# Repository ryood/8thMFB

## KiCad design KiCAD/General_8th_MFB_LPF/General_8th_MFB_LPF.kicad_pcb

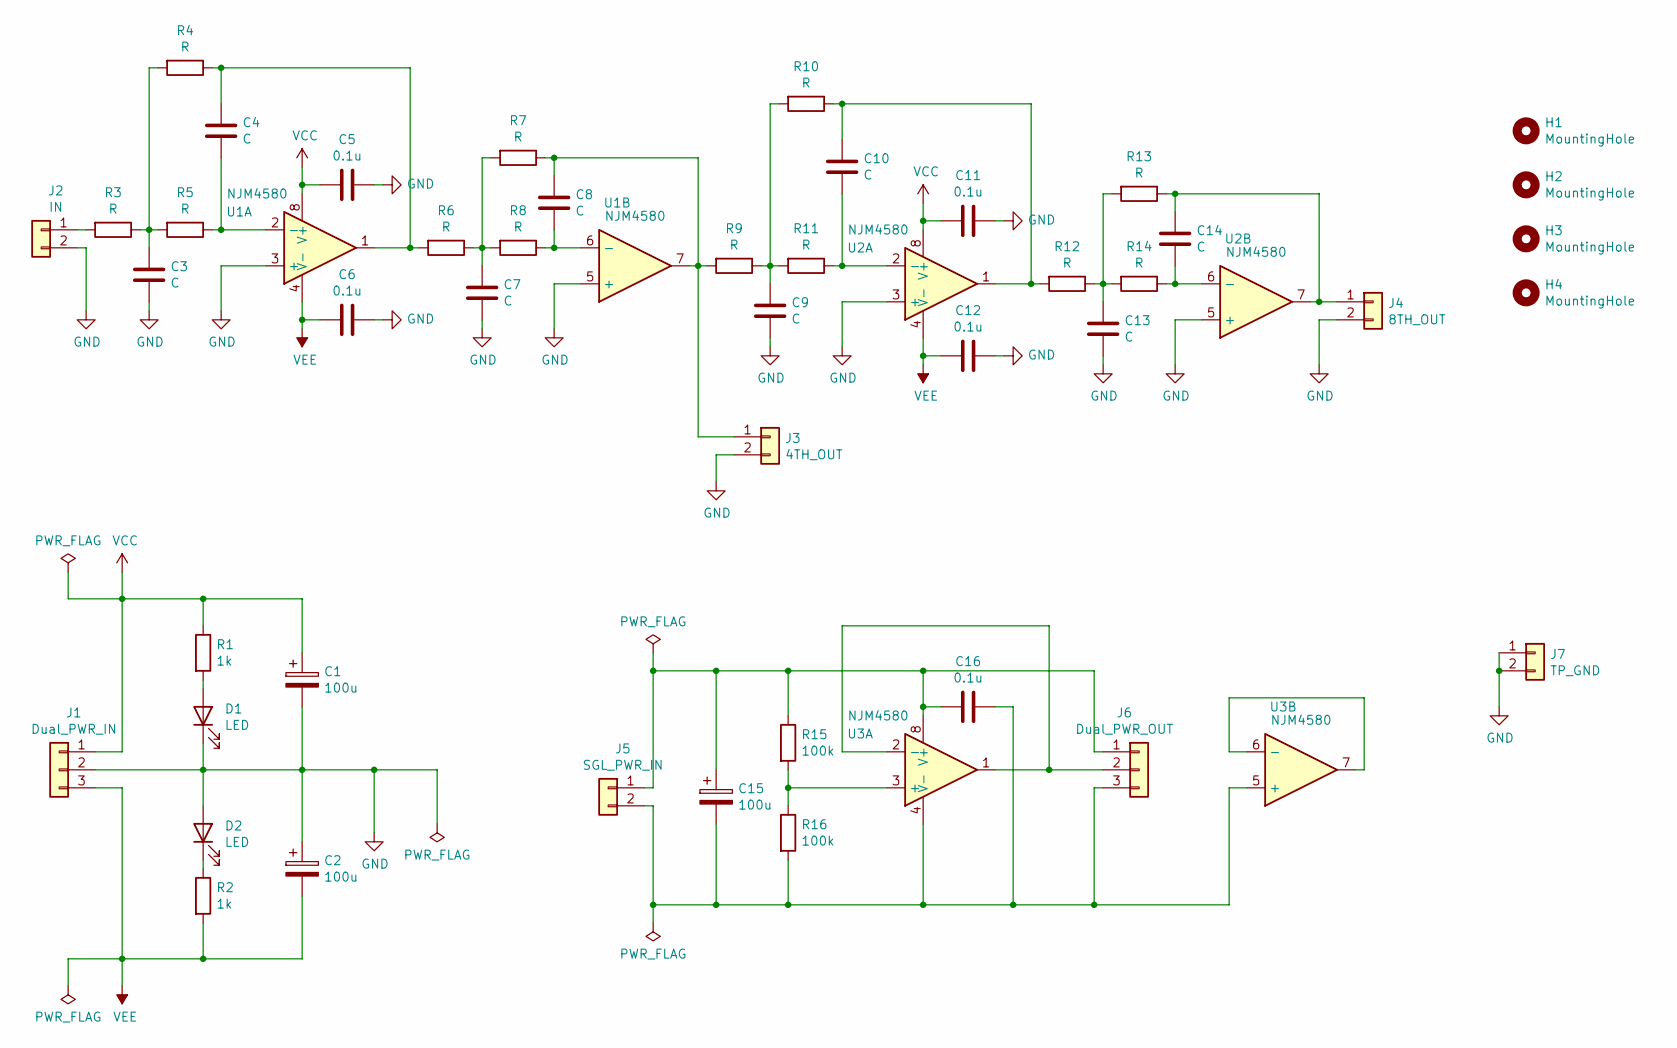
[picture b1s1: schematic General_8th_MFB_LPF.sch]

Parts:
C1, C2, C15: 100u; CP_Radial_D6.3mm_P2.50mm
C3, C4, C7, C8, C9, C10, C13, C14: C; C_Rect_L7.0mm_W3.5mm_P2.50mm_P5.00mm
C5, C6, C11, C12, C16: 0.1u; C_Disc_D3.4mm_W2.1mm_P2.50mm
D1, D2: LED; LED_D3.0mm
H1, H2, H3, H4: MountingHole; MountingHole_3.2mm_M3
J1: Dual_PWR_IN; JST_XH_B3B-XH-A_1x03_P2.50mm_Vertical
J2: IN; JST_XH_B2B-XH-A_1x02_P2.50mm_Vertical
J3: 4TH_OUT; JST_XH_B2B-XH-A_1x02_P2.50mm_Vertical
J4: 8TH_OUT; JST_XH_B2B-XH-A_1x02_P2.50mm_Vertical
J5: SGL_PWR_IN; JST_XH_B2B-XH-A_1x02_P2.50mm_Vertical
J6: Dual_PWR_OUT; JST_XH_B3B-XH-A_1x03_P2.50mm_Vertical
J7: TP_GND; PinHeader_1x02_P2.54mm_Vertical
R1, R2: 1k; R_Axial_DIN0207_L6.3mm_D2.5mm_P7.62mm_Horizontal
R3, R4, R5, R6, R7, R8, R9, R10, R11, R12, R13, R14: R; R_Axial_DIN0207_L6.3mm_D2.5mm_P7.62mm_Horizontal
R15, R16: 100k; R_Axial_DIN0207_L6.3mm_D2.5mm_P7.62mm_Horizontal
U1, U2, U3: NJM4580; DIP-8_W7.62mm_Socket_LongPads

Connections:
GND: C1.2, C2.1, C3.2, C5.1, C6.1, C7.2, C9.2, C11.1, C12.1, C13.2, D1.1 (K), D2.2 (A), J1.2, J2.2, J3.2, J4.2, J7.1, J7.2, U1.3 (+), U1.5 (+), U2.3 (+), U2.5 (+)
unnamed: C3.1, R3.1, R4.2, R5.2
unnamed: C4.1, R4.1, R6.2, U1.1
unnamed: C4.2, R5.1, U1.2 (-)
unnamed: C7.1, R6.1, R7.2, R8.2
unnamed: C8.1, J3.1, R7.1, R9.2, U1.7
unnamed: C8.2, R8.1, U1.6 (-)
unnamed: C9.1, R9.1, R10.2, R11.2
unnamed: C10.1, R10.1, R12.2, U2.1
unnamed: C10.2, R11.1, U2.2 (-)
unnamed: C13.1, R12.1, R13.2, R14.2
unnamed: C14.1, J4.1, R13.1, U2.7
unnamed: C14.2, R14.1, U2.6 (-)
unnamed: C15.1, C16.2, J5.1, J6.1, R15.1, U3.8 (V+)
unnamed: C15.2, C16.1, J5.2, J6.3, R16.2, U3.4 (V-), U3.5 (+)
unnamed: D1.2 (A), R1.2
unnamed: D2.1 (K), R2.1
unnamed: J2.1, R3.2
unnamed: J6.2, U3.1, U3.2 (-)
unnamed: R15.2, R16.1, U3.3 (+)
unnamed: U3.6 (-), U3.7
VCC: C1.1, C5.2, C11.2, J1.1, R1.1, U1.8 (V+), U2.8 (V+)
VEE: C2.2, C6.2, C12.2, J1.3, R2.2, U1.4 (V-), U2.4 (V-)

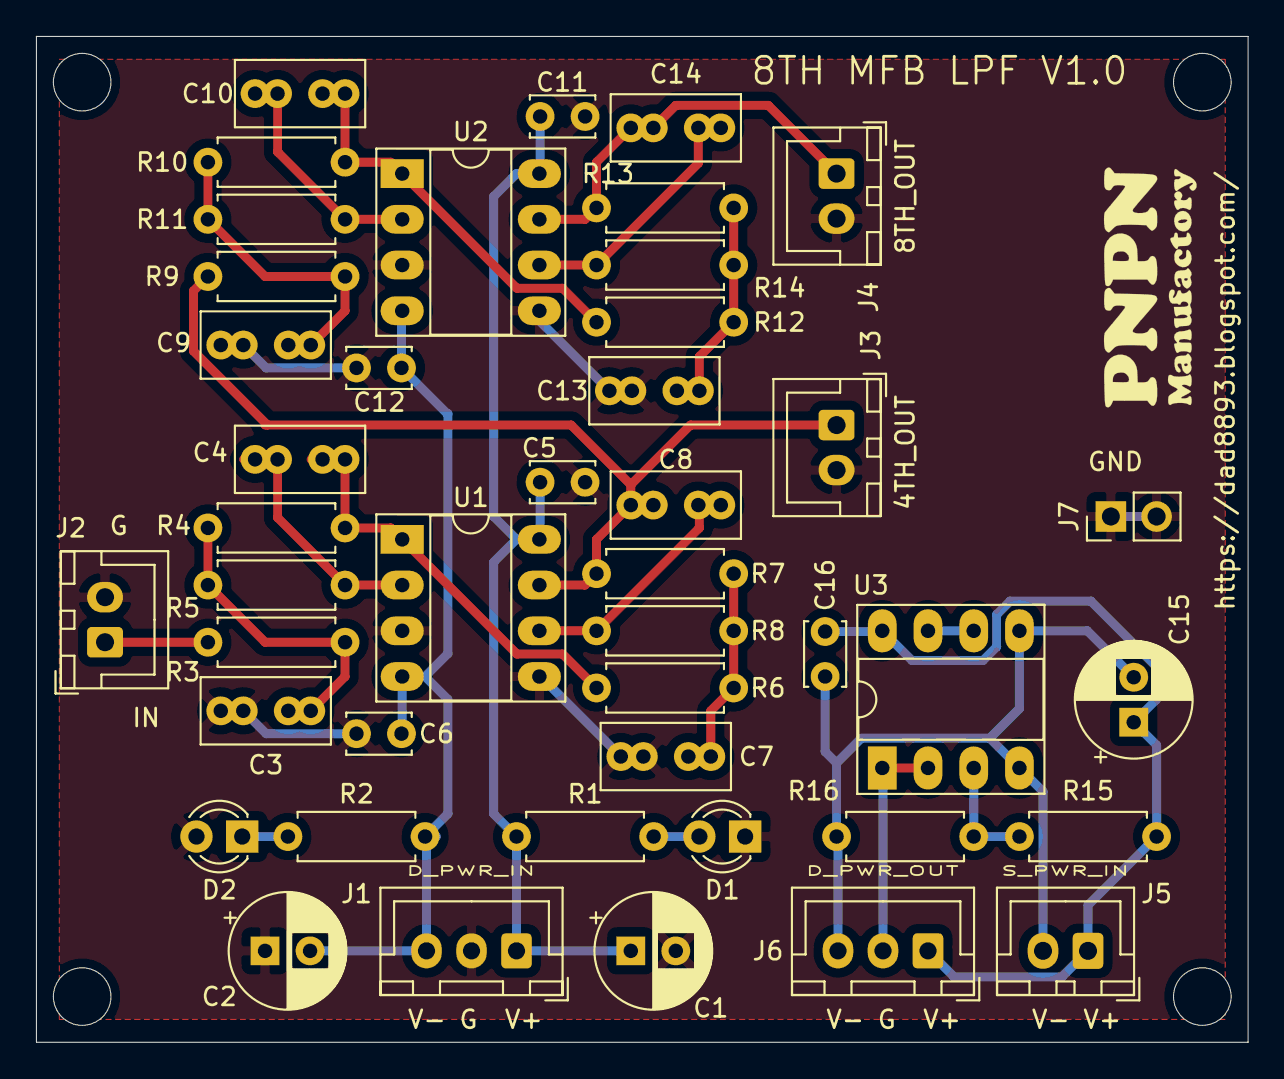
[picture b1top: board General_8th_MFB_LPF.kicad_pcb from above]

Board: 2 copper layers, 67.3 x 55.9 mm, 48 parts (0 on the bottom side), 23 nets.

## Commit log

2020-10-12 Tested with Analog Discovery 2
